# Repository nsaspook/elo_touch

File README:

Firmware to replace Implanter CRT touch monitors with LCD touch monitors. 

The ELO 19" open-frame monitor is the standard for all machines using the 19 inch rack mount as a universal adapter. Originally ELO LCD's were CarrollTouch but that was discontinued so the
emulation now is based on IntelliTouch. Now the old 1939L models are EOL so adding the 199(01)L models as the current replacement.

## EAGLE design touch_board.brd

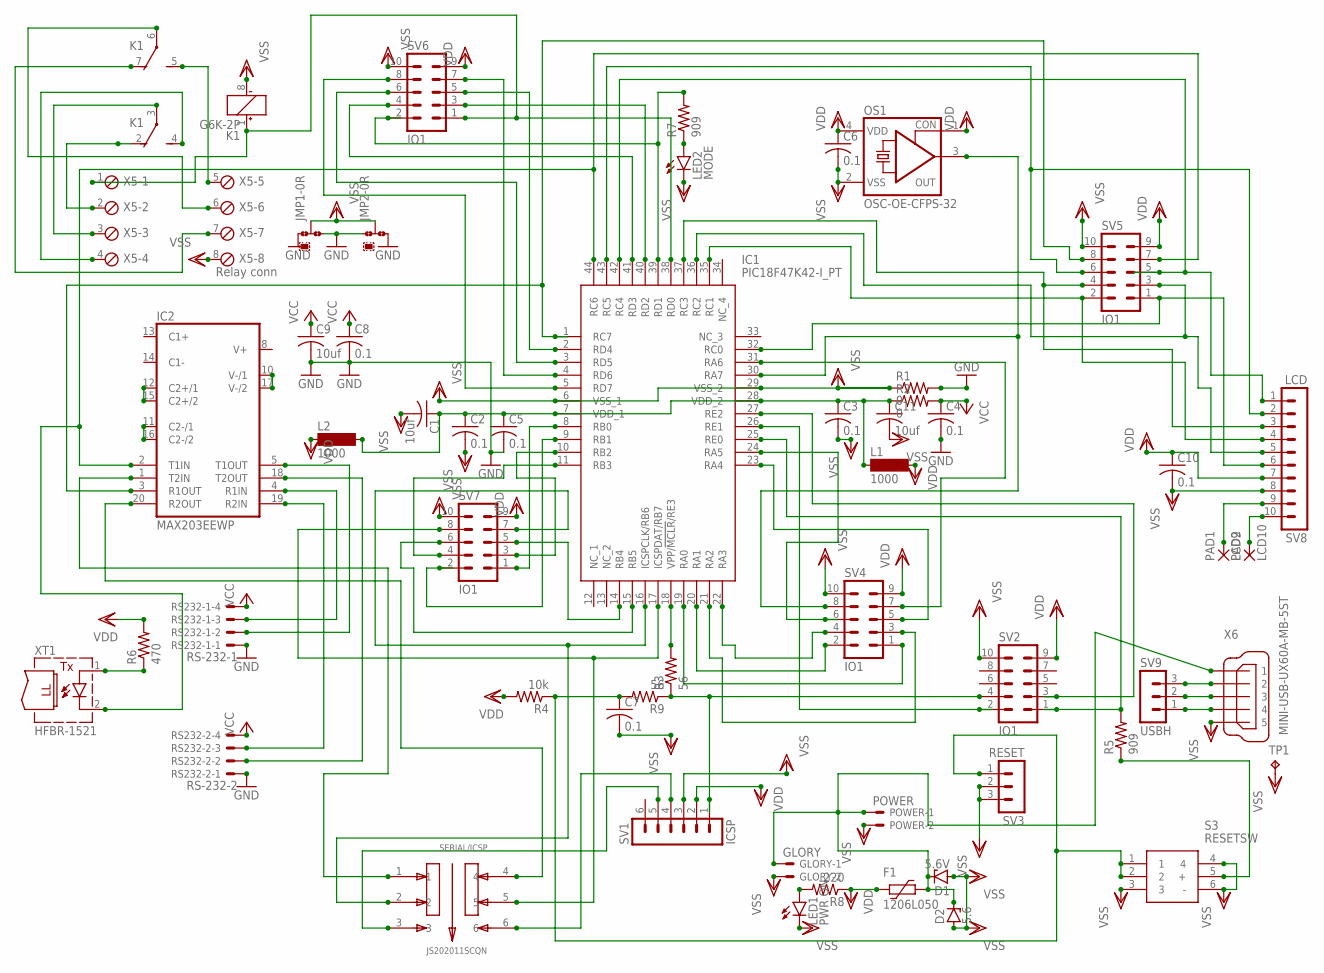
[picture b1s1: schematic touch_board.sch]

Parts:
C1, C9, C11: 10uf; C0805
C2, C3, C4, C5, C6, C7, C8, C10: 0.1; C0805
D1: 5.6V; ZDIO-7.5
D2: 5.6; SMB
F1: 1206L050; 1206L
GLORY: GLORY; 22-23-2021
IC1: PIC18F47K42-I_PT; QFP80P1200X1200X120-44N
IC2: MAX203EEWP; SO20L
JMP1, JMP2: 0R-JUMPA; A0R-JMP
K1: G6K-2P
L1, L2: 1000; SM-1206
LED1: PWR ON; CHIPLED_1206
LED2: MODE; CHIPLED_1206
OS1: OSC-OE-CFPS-32; 7.2X5.2-4-PAD
PAD1: LCD9; SMD1,27-2,54
PAD2: LCD10; SMD1,27-2,54
POWER: POWER; 22-23-2021
R1, R2: 0; R0805
R3, R9: 56; R0805
R4: 10k; R0805
R5, R7: 909; R0805
R6: 470; R0805
R8: 220; R0805
RS232-1: RS-232-1; 22-23-2041
RS232-2: RS-232-2; 22-23-2041
S3: RESETSW; B3W-9_1-LED
SERIAL/ICSP: JS202011SCQN; SW_JS202011SCQN
SV1: ICSP; MA06-1
SV2, SV4, SV5, SV6, SV7: IO1; MA05-2
SV3: RESET; MA03-1
SV8: LCD; MA10-1
SV9: USBH; MA03-1
TP1: TPB1,27; B1,27
X5: Relay conn; 8POL254
X6: MINI-USB-UX60A-MB-5ST; UX60A-MB-5ST
XT1: HFBR-1521; HFBR-15X3

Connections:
GND: C4.2, C5.2, C8.2, C9.2, IC2.6 (GND), IC2.9 (GND), JMP1.1, JMP1.3, JMP2.1, JMP2.3, R1.2, RS232-1.1, RS232-2.1
unnamed: IC1.30 (RA7), OS1.3 (OUT), SV4.8
unnamed: R3.1, R9.1, SV1.1, SV2.4
unnamed: IC1.18 (VPP/!MCLR!/RE3), R3.2
unnamed: IC1.25 (RE0), R5.2, SV2.1
unnamed: IC1.26 (RE1), SV2.2
unnamed: IC1.17 (ICSPDAT/RB7), SERIAL/ICSP.5, SV7.8
unnamed: IC1.16 (ICSPCLK/RB6), SERIAL/ICSP.2, SV7.7
unnamed: IC1.27 (RE2), SV2.3
unnamed: R5.1, S3.5 (+)
unnamed: IC1.39 (RD1), R7.2, SV6.2
unnamed: LED2.A, R7.1
unnamed: IC2.11 (C2-/1), IC2.16 (C2-/2)
unnamed: IC2.10 (V-/1), IC2.17 (V-/2)
unnamed: IC2.12 (C2+/1), IC2.15 (C2+/2)
unnamed: IC2.5 (T1OUT), RS232-1.2
unnamed: IC2.18 (T2OUT), RS232-2.2
unnamed: IC2.4 (R1IN), RS232-1.3
unnamed: IC2.19 (R2IN), RS232-2.3
unnamed: IC2.1 (T2IN), SERIAL/ICSP.1
unnamed: IC1.1 (RC7), IC2.3 (R1OUT), SV5.8
unnamed: IC2.20 (R2OUT), SERIAL/ICSP.4
unnamed: SERIAL/ICSP.6, SV1.4
unnamed: IC1.44 (RC6), IC2.2 (T1IN), SV5.7, XT1.2 (C)
unnamed: R6.1, XT1.1 (A)
unnamed: IC1.19 (RA0), SV4.1
unnamed: IC1.20 (RA1), SV4.2
unnamed: IC1.21 (RA2), SV4.3
unnamed: IC1.22 (RA3), SV4.4
unnamed: IC1.23 (RA4), SV4.5
unnamed: IC1.31 (RA6), SV4.7
unnamed: IC1.24 (RA5), SV4.6
unnamed: IC1.32 (RC0), SV5.1, SV8.6
unnamed: IC1.35 (RC1), SV5.2, SV8.4
unnamed: IC1.36 (RC2), SV5.3, SV8.5
unnamed: IC1.37 (RC3), SV5.4, SV8.3
unnamed: LED1.A, R8.2
unnamed: IC1.43 (RC5), SV5.6, SV8.2
unnamed: K1.2 (O), X5.2
unnamed: IC1.40 (RD2), SV6.3
unnamed: IC1.41 (RD3), SV6.4
unnamed: IC1.2 (RD4), SV6.5
unnamed: IC1.3 (RD5), SV6.6
unnamed: IC1.4 (RD6), SV6.7
unnamed: IC1.5 (RD7), SV6.8
unnamed: IC1.8 (RB0), SV7.1
unnamed: IC1.9 (RB1), SV7.2
unnamed: IC1.10 (RB2), SV7.3
unnamed: IC1.11 (RB3), SV7.4
unnamed: IC1.14 (RB4), SV7.5
unnamed: IC1.15 (RB5), SV7.6
unnamed: IC1.38 (RD0), K1.1 (+), SV6.1, X5.1
unnamed: K1.3, X5.3
unnamed: K1.4 (S), X5.4
unnamed: K1.5 (S), X5.5
unnamed: K1.6, X5.6
unnamed: K1.7 (O), X5.7
unnamed: C1.1, C2.1, C3.1, C5.1, C11.1, IC1.7 (VDD_1), IC1.28 (VDD_2), L1.1, L2.2, R2.1
unnamed: SV9.3, X6.2
unnamed: D1.C, D2.C, F1.1, GLORY.1, POWER.1, X6.1
unnamed: SV9.2, X6.3
unnamed: C7.1, R4.1, R9.2, S3.1, S3.2, SV3.1
unnamed: IC1.42 (RC4), SV5.5, SV8.1
unnamed: SV9.1, X6.4
unnamed: SERIAL/ICSP.3, SV1.5
unnamed: PAD1.1, SV8.9
unnamed: PAD2.1, SV8.10
VCC: C4.1, C8.1, C9.1, IC2.7 (VCC), R2.2, RS232-1.4, RS232-2.4
VDD: C6.1, C10.1, F1.2, L1.2, L2.1, OS1.1 (CON), OS1.4 (VDD), R4.2, R6.2, R8.1, SV1.2, SV2.9, SV4.9, SV5.9, SV6.9, SV7.9, SV8.7
VSS: C1.2, C2.2, C3.2, C6.2, C7.2, C10.2, C11.2, D1.A, D2.A, GLORY.2, IC1.6 (VSS_1), IC1.29 (VSS_2), JMP1.2, JMP2.2, K1.8 (-), LED1.C, LED2.C, OS1.2 (VSS), POWER.2, R1.1, S3.3, S3.4, S3.6 (-), SV1.3, SV2.10, SV3.2, SV3.3, SV4.10, SV5.10, SV6.10, SV7.10, SV8.8, TP1.TP, X5.8, X6.5

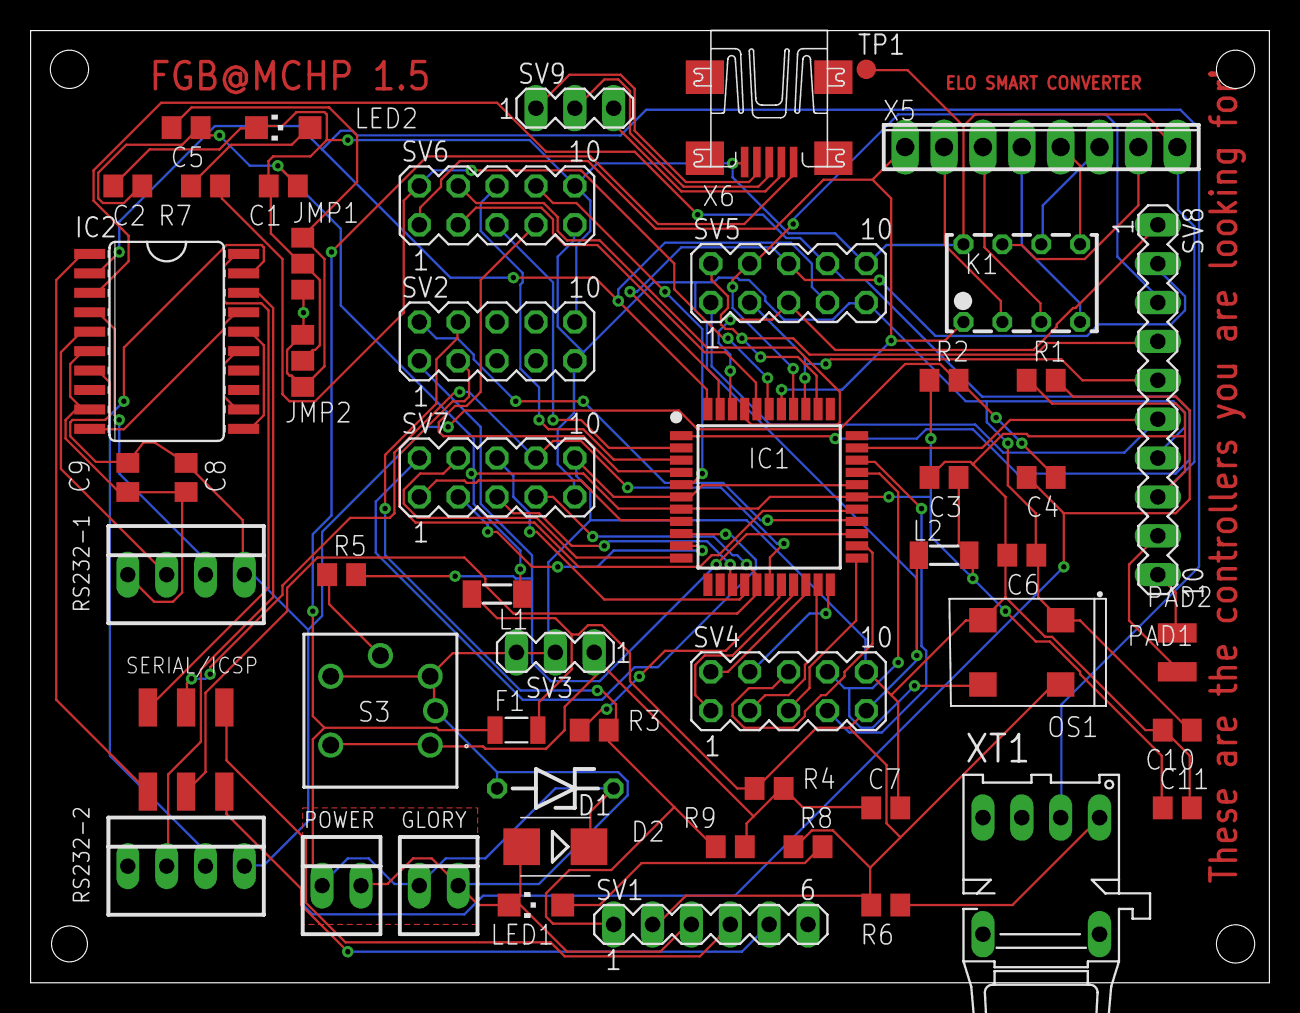
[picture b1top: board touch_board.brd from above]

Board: 2 copper layers, 81.0 x 62.2 mm, 54 parts (0 on the bottom side), 70 nets.

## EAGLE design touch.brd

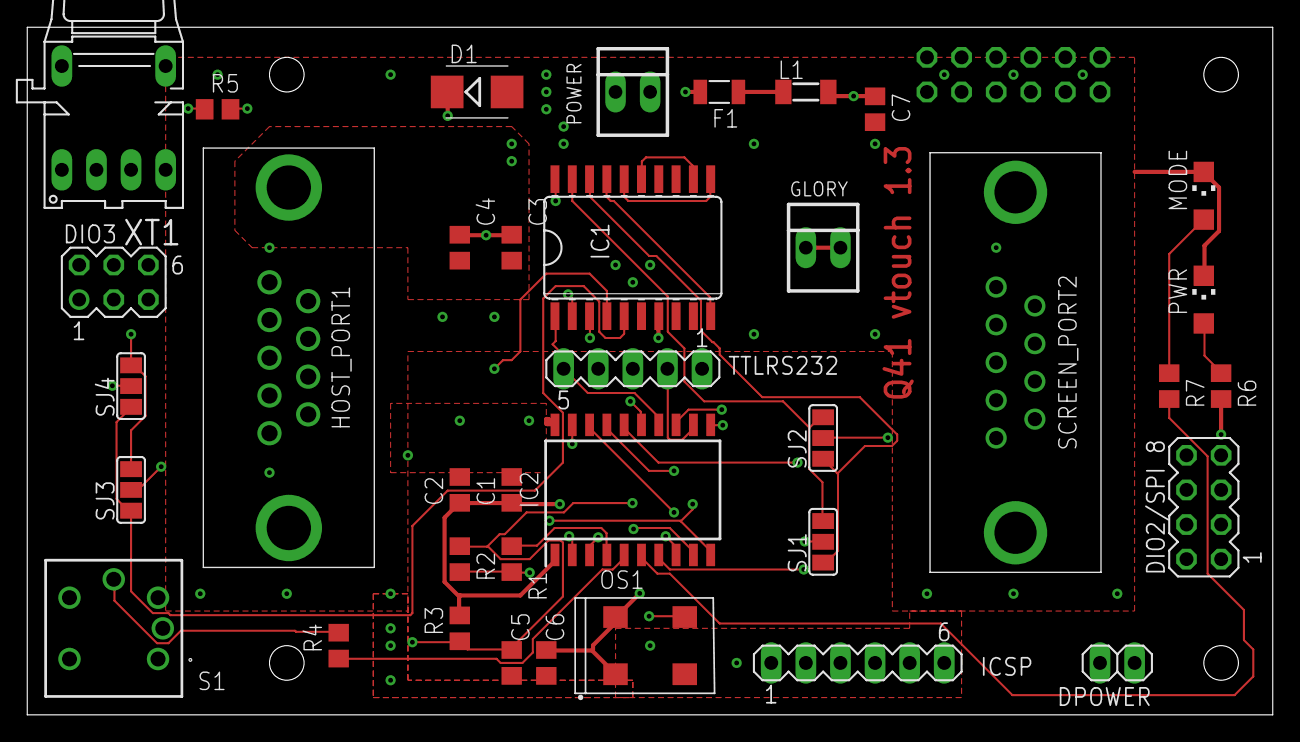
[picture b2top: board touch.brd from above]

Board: 4 copper layers, 91.4 x 50.5 mm, 38 parts (1 on the bottom side), 39 nets.

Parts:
C1: 0.1uf; C0805
C2, C4, C7: 10uf; C0805
C3, C5, C6: 0.1; C0805
D1: 5.6V; SMB
DIO2/SPI: MA04-2
DIO3: MA03-2
DPOWER: DPOWER; 1X02
F1: 0.75A; 1206L
GLORY: GLORY; 22-23-2021
HOST_PORT1: 2301838-2; 23018382
IC1: MAX203ECWP; SO20L
IC2: PIC18F14Q41-I_SO; SOIC127P1030X265-20N
ICSP: MA06-1
L1: 1000; SM-1206
MODE: Green; CHIPLED_1206
OS1: OSC-OE-CFPS-32; 7.2X5.2-4-PAD
PMOD: Pmod; MA06-2
POWER: 22-23-2021
PWR: Green; CHIPLED_1206
R1, R2: 56; R0805
R3: 10K; R0805
R4, R6, R7: 1.2k; R0805
R5: 200; R0805
S1: B3W-9000-Y1N; B3W-9_1-LED
SCREEN_PORT2: 2301826-2; 23018262
SJ1, SJ2, SJ3, SJ4: SJ_2
TTLRS232: MA05-1
XT1: HFBR-1521; HFBR-15X3

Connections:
CLKIN: DIO3.4, IC2.2, OS1.3
CS: DIO2/SPI.6, IC2.11, PMOD.1
DB0: IC2.19, ICSP.4
DB1: IC2.18, ICSP.5
GND: C1.2, C2.2, C3.2, C4.2, C5.2, C6.2, C7.2, D1.A, DIO2/SPI.2, DIO2/SPI.4, DIO3.2, DPOWER.2, HOST_PORT1.5, HOST_PORT1.MH1, HOST_PORT1.MH2, IC1.6, IC1.9, IC2.20, ICSP.3, MODE.C, OS1.2, PMOD.9, PMOD.10, POWER.2, PWR.C, S1.3, S1.4, S1.6, SCREEN_PORT2.5, SCREEN_PORT2.MH1, SCREEN_PORT2.MH2, TTLRS232.1, XT1.2
MIN0: DIO2/SPI.1, IC2.16
MIN1: DIO2/SPI.3, IC2.7
MISC: DIO3.3, IC2.10, PMOD.2
MISO: DIO2/SPI.7, IC2.13, PMOD.5
MLED: IC2.6, R7.2
MOSI: DIO2/SPI.5, IC2.17, PMOD.3
unnamed: SCREEN_PORT2.3, SJ2.2
unnamed: SCREEN_PORT2.2, SJ1.2
unnamed: HOST_PORT1.2, SJ4.2
unnamed: HOST_PORT1.3, SJ3.2
unnamed: IC1.12, IC1.15
unnamed: IC1.11, IC1.16
unnamed: IC1.10, IC1.17
unnamed: IC1.5, SJ3.1, SJ4.1
unnamed: IC1.4, SJ3.3, SJ4.3
unnamed: IC1.18, SJ1.1, SJ2.1
unnamed: IC1.19, SJ1.3, SJ2.3
unnamed: IC2.4, R1.2
unnamed: F1.2, POWER.1
unnamed: MODE.A, R7.1
unnamed: R4.2, S1.5
unnamed: R5.1, XT1.1
unnamed: F1.1, L1.1
unnamed: PWR.A, R6.1
PGM: ICSP.1, R1.1, R2.2
RELAY: DIO3.1, IC2.9, PMOD.4
RLED: IC2.5, R4.1
RX1: IC1.3, IC2.12, TTLRS232.2
RX2: IC1.20, IC2.15, TTLRS232.4
SCK: DIO2/SPI.8, IC2.3, PMOD.7
SMCLEAR: C5.1, DIO3.5, PMOD.6, R2.1, R3.1, S1.1, S1.2
TX1: IC1.2, IC2.8, PMOD.8, R5.2, TTLRS232.3
TX2: IC1.1, IC2.14, TTLRS232.5
VCC: C1.1, C2.1, C3.1, C4.1, C6.1, C7.1, D1.C, DIO3.6, DPOWER.1, GLORY.1, GLORY.2, IC1.7, IC2.1, ICSP.2, L1.2, OS1.1, OS1.4, PMOD.11, PMOD.12, R3.2, R6.2

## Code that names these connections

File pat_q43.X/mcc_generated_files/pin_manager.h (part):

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// get/set LD0 aliases
#define LD0_TRIS                 TRISAbits.TRISA0
#define LD0_LAT                  LATAbits.LATA0
#define LD0_PORT                 PORTAbits.RA0
#define LD0_WPU                  WPUAbits.WPUA0
#define LD0_OD                   ODCONAbits.ODCA0
#define LD0_ANS                  ANSELAbits.ANSELA0
#define LD0_SetHigh()            do { LATAbits.LATA0 = 1; } while(0)
#define LD0_SetLow()             do { LATAbits.LATA0 = 0; } while(0)
#define LD0_Toggle()             do { LATAbits.LATA0 = ~LATAbits.LATA0; } while(0)
#define LD0_GetValue()           PORTAbits.RA0
#define LD0_SetDigitalInput()    do { TRISAbits.TRISA0 = 1; } while(0)
#define LD0_SetDigitalOutput()   do { TRISAbits.TRISA0 = 0; } while(0)
#define LD0_SetPullup()          do { WPUAbits.WPUA0 = 1; } while(0)
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// get/set LD1 aliases
#define LD1_TRIS                 TRISAbits.TRISA1
#define LD1_LAT                  LATAbits.LATA1
#define LD1_PORT                 PORTAbits.RA1
#define LD1_WPU                  WPUAbits.WPUA1
#define LD1_OD                   ODCONAbits.ODCA1
#define LD1_ANS                  ANSELAbits.ANSELA1
#define LD1_SetHigh()            do { LATAbits.LATA1 = 1; } while(0)
#define LD1_SetLow()             do { LATAbits.LATA1 = 0; } while(0)
#define LD1_Toggle()             do { LATAbits.LATA1 = ~LATAbits.LATA1; } while(0)
#define LD1_GetValue()           PORTAbits.RA1
#define LD1_SetDigitalInput()    do { TRISAbits.TRISA1 = 1; } while(0)
#define LD1_SetDigitalOutput()   do { TRISAbits.TRISA1 = 0; } while(0)
#define LD1_SetPullup()          do { WPUAbits.WPUA1 = 1; } while(0)
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// get/set LD2 aliases
#define LD2_TRIS                 TRISAbits.TRISA2
#define LD2_LAT                  LATAbits.LATA2
#define LD2_PORT                 PORTAbits.RA2
#define LD2_WPU                  WPUAbits.WPUA2
#define LD2_OD                   ODCONAbits.ODCA2
#define LD2_ANS                  ANSELAbits.ANSELA2
#define LD2_SetHigh()            do { LATAbits.LATA2 = 1; } while(0)
#define LD2_SetLow()             do { LATAbits.LATA2 = 0; } while(0)
#define LD2_Toggle()             do { LATAbits.LATA2 = ~LATAbits.LATA2; } while(0)
#define LD2_GetValue()           PORTAbits.RA2
#define LD2_SetDigitalInput()    do { TRISAbits.TRISA2 = 1; } while(0)
#define LD2_SetDigitalOutput()   do { TRISAbits.TRISA2 = 0; } while(0)
#define LD2_SetPullup()          do { WPUAbits.WPUA2 = 1; } while(0)
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// get/set LD3 aliases
#define LD3_TRIS                 TRISAbits.TRISA3
#define LD3_LAT                  LATAbits.LATA3
#define LD3_PORT                 PORTAbits.RA3
#define LD3_WPU                  WPUAbits.WPUA3
#define LD3_OD                   ODCONAbits.ODCA3
#define LD3_ANS                  ANSELAbits.ANSELA3
#define LD3_SetHigh()            do { LATAbits.LATA3 = 1; } while(0)
#define LD3_SetLow()             do { LATAbits.LATA3 = 0; } while(0)
#define LD3_Toggle()             do { LATAbits.LATA3 = ~LATAbits.LATA3; } while(0)
#define LD3_GetValue()           PORTAbits.RA3
#define LD3_SetDigitalInput()    do { TRISAbits.TRISA3 = 1; } while(0)
#define LD3_SetDigitalOutput()   do { TRISAbits.TRISA3 = 0; } while(0)
#define LD3_SetPullup()          do { WPUAbits.WPUA3 = 1; } while(0)
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// get/set SW0 aliases
#define SW0_TRIS                 TRISBbits.TRISB0
#define SW0_LAT                  LATBbits.LATB0
#define SW0_PORT                 PORTBbits.RB0
#define SW0_WPU                  WPUBbits.WPUB0
#define SW0_OD                   ODCONBbits.ODCB0
#define SW0_ANS                  ANSELBbits.ANSELB0
#define SW0_SetHigh()            do { LATBbits.LATB0 = 1; } while(0)
#define SW0_SetLow()             do { LATBbits.LATB0 = 0; } while(0)
#define SW0_Toggle()             do { LATBbits.LATB0 = ~LATBbits.LATB0; } while(0)
#define SW0_GetValue()           PORTBbits.RB0
#define SW0_SetDigitalInput()    do { TRISBbits.TRISB0 = 1; } while(0)
#define SW0_SetDigitalOutput()   do { TRISBbits.TRISB0 = 0; } while(0)
#define SW0_SetPullup()          do { WPUBbits.WPUB0 = 1; } while(0)
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// get/set SW1 aliases
#define SW1_TRIS                 TRISBbits.TRISB1
#define SW1_LAT                  LATBbits.LATB1
#define SW1_PORT                 PORTBbits.RB1
#define SW1_WPU                  WPUBbits.WPUB1
#define SW1_OD                   ODCONBbits.ODCB1
#define SW1_ANS                  ANSELBbits.ANSELB1
#define SW1_SetHigh()            do { LATBbits.LATB1 = 1; } while(0)
#define SW1_SetLow()             do { LATBbits.LATB1 = 0; } while(0)
#define SW1_Toggle()             do { LATBbits.LATB1 = ~LATBbits.LATB1; } while(0)
#define SW1_GetValue()           PORTBbits.RB1
#define SW1_SetDigitalInput()    do { TRISBbits.TRISB1 = 1; } while(0)
#define SW1_SetDigitalOutput()   do { TRISBbits.TRISB1 = 0; } while(0)
#define SW1_SetPullup()          do { WPUBbits.WPUB1 = 1; } while(0)
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// get/set SW2 aliases
#define SW2_TRIS                 TRISBbits.TRISB2
#define SW2_LAT                  LATBbits.LATB2
#define SW2_PORT                 PORTBbits.RB2
#define SW2_WPU                  WPUBbits.WPUB2
#define SW2_OD                   ODCONBbits.ODCB2
#define SW2_ANS                  ANSELBbits.ANSELB2
#define SW2_SetHigh()            do { LATBbits.LATB2 = 1; } while(0)
#define SW2_SetLow()             do { LATBbits.LATB2 = 0; } while(0)
#define SW2_Toggle()             do { LATBbits.LATB2 = ~LATBbits.LATB2; } while(0)
#define SW2_GetValue()           PORTBbits.RB2
#define SW2_SetDigitalInput()    do { TRISBbits.TRISB2 = 1; } while(0)
#define SW2_SetDigitalOutput()   do { TRISBbits.TRISB2 = 0; } while(0)
#define SW2_SetPullup()          do { WPUBbits.WPUB2 = 1; } while(0)
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// get/set SW3 aliases
#define SW3_TRIS                 TRISBbits.TRISB3
#define SW3_LAT                  LATBbits.LATB3
#define SW3_PORT                 PORTBbits.RB3
#define SW3_WPU                  WPUBbits.WPUB3
#define SW3_OD                   ODCONBbits.ODCB3
#define SW3_ANS                  ANSELBbits.ANSELB3
#define SW3_SetHigh()            do { LATBbits.LATB3 = 1; } while(0)
#define SW3_SetLow()             do { LATBbits.LATB3 = 0; } while(0)
#define SW3_Toggle()             do { LATBbits.LATB3 = ~LATBbits.LATB3; } while(0)
#define SW3_GetValue()           PORTBbits.RB3
#define SW3_SetDigitalInput()    do { TRISBbits.TRISB3 = 1; } while(0)
#define SW3_SetDigitalOutput()   do { TRISBbits.TRISB3 = 0; } while(0)
#define SW3_SetPullup()          do { WPUBbits.WPUB3 = 1; } while(0)
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// get/set ID0 aliases
#define ID0_TRIS                 TRISBbits.TRISB4
#define ID0_LAT                  LATBbits.LATB4
#define ID0_PORT                 PORTBbits.RB4
#define ID0_WPU                  WPUBbits.WPUB4
#define ID0_OD                   ODCONBbits.ODCB4
#define ID0_ANS                  ANSELBbits.ANSELB4
#define ID0_SetHigh()            do { LATBbits.LATB4 = 1; } while(0)
#define ID0_SetLow()             do { LATBbits.LATB4 = 0; } while(0)
#define ID0_Toggle()             do { LATBbits.LATB4 = ~LATBbits.LATB4; } while(0)
#define ID0_GetValue()           PORTBbits.RB4
#define ID0_SetDigitalInput()    do { TRISBbits.TRISB4 = 1; } while(0)
#define ID0_SetDigitalOutput()   do { TRISBbits.TRISB4 = 0; } while(0)
#define ID0_SetPullup()          do { WPUBbits.WPUB4 = 1; } while(0)
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// get/set ID1 aliases
#define ID1_TRIS                 TRISBbits.TRISB5
#define ID1_LAT                  LATBbits.LATB5
#define ID1_PORT                 PORTBbits.RB5
#define ID1_WPU                  WPUBbits.WPUB5
#define ID1_OD                   ODCONBbits.ODCB5
#define ID1_ANS                  ANSELBbits.ANSELB5
#define ID1_SetHigh()            do { LATBbits.LATB5 = 1; } while(0)
#define ID1_SetLow()             do { LATBbits.LATB5 = 0; } while(0)
#define ID1_Toggle()             do { LATBbits.LATB5 = ~LATBbits.LATB5; } while(0)
#define ID1_GetValue()           PORTBbits.RB5
#define ID1_SetDigitalInput()    do { TRISBbits.TRISB5 = 1; } while(0)
#define ID1_SetDigitalOutput()   do { TRISBbits.TRISB5 = 0; } while(0)
#define ID1_SetPullup()          do { WPUBbits.WPUB5 = 1; } while(0)
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// get/set ID2 aliases
#define ID2_TRIS                 TRISBbits.TRISB6
#define ID2_LAT                  LATBbits.LATB6
#define ID2_PORT                 PORTBbits.RB6
#define ID2_WPU                  WPUBbits.WPUB6
#define ID2_OD                   ODCONBbits.ODCB6
#define ID2_ANS                  ANSELBbits.ANSELB6
#define ID2_SetHigh()            do { LATBbits.LATB6 = 1; } while(0)
#define ID2_SetLow()             do { LATBbits.LATB6 = 0; } while(0)
#define ID2_Toggle()             do { LATBbits.LATB6 = ~LATBbits.LATB6; } while(0)
#define ID2_GetValue()           PORTBbits.RB6
#define ID2_SetDigitalInput()    do { TRISBbits.TRISB6 = 1; } while(0)
#define ID2_SetDigitalOutput()   do { TRISBbits.TRISB6 = 0; } while(0)
#define ID2_SetPullup()          do { WPUBbits.WPUB6 = 1; } while(0)
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// get/set ID3 aliases
#define ID3_TRIS                 TRISBbits.TRISB7
#define ID3_LAT                  LATBbits.LATB7
#define ID3_PORT                 PORTBbits.RB7
#define ID3_WPU                  WPUBbits.WPUB7
#define ID3_OD                   ODCONBbits.ODCB7
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
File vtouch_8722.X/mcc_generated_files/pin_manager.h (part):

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// get/set JMP1 aliases
#define JMP1_TRIS                 TRISAbits.TRISA0
#define JMP1_LAT                  LATAbits.LATA0
#define JMP1_PORT                 PORTAbits.RA0
#define JMP1_WPU                  WPUAbits.WPUA0
#define JMP1_OD                   ODCONAbits.ODCA0
#define JMP1_ANS                  ANSELAbits.ANSELA0
#define JMP1_SetHigh()            do { LATAbits.LATA0 = 1; } while(0)
#define JMP1_SetLow()             do { LATAbits.LATA0 = 0; } while(0)
#define JMP1_Toggle()             do { LATAbits.LATA0 = ~LATAbits.LATA0; } while(0)
#define JMP1_GetValue()           PORTAbits.RA0
#define JMP1_SetDigitalInput()    do { TRISAbits.TRISA0 = 1; } while(0)
#define JMP1_SetDigitalOutput()   do { TRISAbits.TRISA0 = 0; } while(0)
#define JMP1_SetPullup()          do { WPUAbits.WPUA0 = 1; } while(0)
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// get/set JMP1SET aliases
#define JMP1SET_TRIS                 TRISAbits.TRISA1
#define JMP1SET_LAT                  LATAbits.LATA1
#define JMP1SET_PORT                 PORTAbits.RA1
#define JMP1SET_WPU                  WPUAbits.WPUA1
#define JMP1SET_OD                   ODCONAbits.ODCA1
#define JMP1SET_ANS                  ANSELAbits.ANSELA1
#define JMP1SET_SetHigh()            do { LATAbits.LATA1 = 1; } while(0)
#define JMP1SET_SetLow()             do { LATAbits.LATA1 = 0; } while(0)
#define JMP1SET_Toggle()             do { LATAbits.LATA1 = ~LATAbits.LATA1; } while(0)
#define JMP1SET_GetValue()           PORTAbits.RA1
#define JMP1SET_SetDigitalInput()    do { TRISAbits.TRISA1 = 1; } while(0)
#define JMP1SET_SetDigitalOutput()   do { TRISAbits.TRISA1 = 0; } while(0)
#define JMP1SET_SetPullup()          do { WPUAbits.WPUA1 = 1; } while(0)
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// get/set JMP2 aliases
#define JMP2_TRIS                 TRISAbits.TRISA2
#define JMP2_LAT                  LATAbits.LATA2
#define JMP2_PORT                 PORTAbits.RA2
#define JMP2_WPU                  WPUAbits.WPUA2
#define JMP2_OD                   ODCONAbits.ODCA2
#define JMP2_ANS                  ANSELAbits.ANSELA2
#define JMP2_SetHigh()            do { LATAbits.LATA2 = 1; } while(0)
#define JMP2_SetLow()             do { LATAbits.LATA2 = 0; } while(0)
#define JMP2_Toggle()             do { LATAbits.LATA2 = ~LATAbits.LATA2; } while(0)
#define JMP2_GetValue()           PORTAbits.RA2
#define JMP2_SetDigitalInput()    do { TRISAbits.TRISA2 = 1; } while(0)
#define JMP2_SetDigitalOutput()   do { TRISAbits.TRISA2 = 0; } while(0)
#define JMP2_SetPullup()          do { WPUAbits.WPUA2 = 1; } while(0)
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// get/set JMP2SET aliases
#define JMP2SET_TRIS                 TRISAbits.TRISA3
#define JMP2SET_LAT                  LATAbits.LATA3
#define JMP2SET_PORT                 PORTAbits.RA3
#define JMP2SET_WPU                  WPUAbits.WPUA3
#define JMP2SET_OD                   ODCONAbits.ODCA3
#define JMP2SET_ANS                  ANSELAbits.ANSELA3
#define JMP2SET_SetHigh()            do { LATAbits.LATA3 = 1; } while(0)
#define JMP2SET_SetLow()             do { LATAbits.LATA3 = 0; } while(0)
#define JMP2SET_Toggle()             do { LATAbits.LATA3 = ~LATAbits.LATA3; } while(0)
#define JMP2SET_GetValue()           PORTAbits.RA3
#define JMP2SET_SetDigitalInput()    do { TRISAbits.TRISA3 = 1; } while(0)
#define JMP2SET_SetDigitalOutput()   do { TRISAbits.TRISA3 = 0; } while(0)
#define JMP2SET_SetPullup()          do { WPUAbits.WPUA3 = 1; } while(0)
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// get/set CAM_R aliases
#define CAM_R_TRIS                 TRISBbits.TRISB0
#define CAM_R_LAT                  LATBbits.LATB0
#define CAM_R_PORT                 PORTBbits.RB0
#define CAM_R_WPU                  WPUBbits.WPUB0
#define CAM_R_OD                   ODCONBbits.ODCB0
#define CAM_R_ANS                  ANSELBbits.ANSELB0
#define CAM_R_SetHigh()            do { LATBbits.LATB0 = 1; } while(0)
#define CAM_R_SetLow()             do { LATBbits.LATB0 = 0; } while(0)
#define CAM_R_Toggle()             do { LATBbits.LATB0 = ~LATBbits.LATB0; } while(0)
#define CAM_R_GetValue()           PORTBbits.RB0
#define CAM_R_SetDigitalInput()    do { TRISBbits.TRISB0 = 1; } while(0)
#define CAM_R_SetDigitalOutput()   do { TRISBbits.TRISB0 = 0; } while(0)
#define CAM_R_SetPullup()          do { WPUBbits.WPUB0 = 1; } while(0)
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// get/set CAM_R1 aliases
#define CAM_R1_TRIS                 TRISBbits.TRISB1
#define CAM_R1_LAT                  LATBbits.LATB1
#define CAM_R1_PORT                 PORTBbits.RB1
#define CAM_R1_WPU                  WPUBbits.WPUB1
#define CAM_R1_OD                   ODCONBbits.ODCB1
#define CAM_R1_ANS                  ANSELBbits.ANSELB1
#define CAM_R1_SetHigh()            do { LATBbits.LATB1 = 1; } while(0)
#define CAM_R1_SetLow()             do { LATBbits.LATB1 = 0; } while(0)
#define CAM_R1_Toggle()             do { LATBbits.LATB1 = ~LATBbits.LATB1; } while(0)
#define CAM_R1_GetValue()           PORTBbits.RB1
#define CAM_R1_SetDigitalInput()    do { TRISBbits.TRISB1 = 1; } while(0)
#define CAM_R1_SetDigitalOutput()   do { TRISBbits.TRISB1 = 0; } while(0)
#define CAM_R1_SetPullup()          do { WPUBbits.WPUB1 = 1; } while(0)
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#define RB6_SetHigh()            do { LATBbits.LATB6 = 1; } while(0)
#define RB6_SetLow()             do { LATBbits.LATB6 = 0; } while(0)
#define RB6_Toggle()             do { LATBbits.LATB6 = ~LATBbits.LATB6; } while(0)
#define RB6_GetValue()              PORTBbits.RB6
#define RB6_SetDigitalInput()    do { TRISBbits.TRISB6 = 1; } while(0)
#define RB6_SetDigitalOutput()   do { TRISBbits.TRISB6 = 0; } while(0)
#define RB6_SetPullup()             do { WPUBbits.WPUB6 = 1; } while(0)
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#define RB7_SetHigh()            do { LATBbits.LATB7 = 1; } while(0)
#define RB7_SetLow()             do { LATBbits.LATB7 = 0; } while(0)
#define RB7_Toggle()             do { LATBbits.LATB7 = ~LATBbits.LATB7; } while(0)
#define RB7_GetValue()              PORTBbits.RB7
#define RB7_SetDigitalInput()    do { TRISBbits.TRISB7 = 1; } while(0)
#define RB7_SetDigitalOutput()   do { TRISBbits.TRISB7 = 0; } while(0)
#define RB7_SetPullup()             do { WPUBbits.WPUB7 = 1; } while(0)
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// get/set RS aliases
#define RS_TRIS                 TRISCbits.TRISC1
#define RS_LAT                  LATCbits.LATC1
#define RS_PORT                 PORTCbits.RC1
#define RS_WPU                  WPUCbits.WPUC1
#define RS_OD                   ODCONCbits.ODCC1
#define RS_ANS                  ANSELCbits.ANSELC1
#define RS_SetHigh()            do { LATCbits.LATC1 = 1; } while(0)
#define RS_SetLow()             do { LATCbits.LATC1 = 0; } while(0)
#define RS_Toggle()             do { LATCbits.LATC1 = ~LATCbits.LATC1; } while(0)
#define RS_GetValue()           PORTCbits.RC1
#define RS_SetDigitalInput()    do { TRISCbits.TRISC1 = 1; } while(0)
#define RS_SetDigitalOutput()   do { TRISCbits.TRISC1 = 0; } while(0)
#define RS_SetPullup()          do { WPUCbits.WPUC1 = 1; } while(0)
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// get/set CSB aliases
#define CSB_TRIS                 TRISCbits.TRISC2
#define CSB_LAT                  LATCbits.LATC2
#define CSB_PORT                 PORTCbits.RC2
#define CSB_WPU                  WPUCbits.WPUC2
#define CSB_OD                   ODCONCbits.ODCC2
#define CSB_ANS                  ANSELCbits.ANSELC2
#define CSB_SetHigh()            do { LATCbits.LATC2 = 1; } while(0)
#define CSB_SetLow()             do { LATCbits.LATC2 = 0; } while(0)
#define CSB_Toggle()             do { LATCbits.LATC2 = ~LATCbits.LATC2; } while(0)
#define CSB_GetValue()           PORTCbits.RC2
#define CSB_SetDigitalInput()    do { TRISCbits.TRISC2 = 1; } while(0)
#define CSB_SetDigitalOutput()   do { TRISCbits.TRISC2 = 0; } while(0)
#define CSB_SetPullup()          do { WPUCbits.WPUC2 = 1; } while(0)
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#define RC3_SetHigh()            do { LATCbits.LATC3 = 1; } while(0)
#define RC3_SetLow()             do { LATCbits.LATC3 = 0; } while(0)
#define RC3_Toggle()             do { LATCbits.LATC3 = ~LATCbits.LATC3; } while(0)
#define RC3_GetValue()              PORTCbits.RC3
#define RC3_SetDigitalInput()    do { TRISCbits.TRISC3 = 1; } while(0)
#define RC3_SetDigitalOutput()   do { TRISCbits.TRISC3 = 0; } while(0)
#define RC3_SetPullup()             do { WPUCbits.WPUC3 = 1; } while(0)
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#define RC4_SetHigh()            do { LATCbits.LATC4 = 1; } while(0)
#define RC4_SetLow()             do { LATCbits.LATC4 = 0; } while(0)
#define RC4_Toggle()             do { LATCbits.LATC4 = ~LATCbits.LATC4; } while(0)
#define RC4_GetValue()              PORTCbits.RC4
#define RC4_SetDigitalInput()    do { TRISCbits.TRISC4 = 1; } while(0)
#define RC4_SetDigitalOutput()   do { TRISCbits.TRISC4 = 0; } while(0)
#define RC4_SetPullup()             do { WPUCbits.WPUC4 = 1; } while(0)
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#define RC5_SetHigh()            do { LATCbits.LATC5 = 1; } while(0)
#define RC5_SetLow()             do { LATCbits.LATC5 = 0; } while(0)
#define RC5_Toggle()             do { LATCbits.LATC5 = ~LATCbits.LATC5; } while(0)
#define RC5_GetValue()              PORTCbits.RC5
#define RC5_SetDigitalInput()    do { TRISCbits.TRISC5 = 1; } while(0)
#define RC5_SetDigitalOutput()   do { TRISCbits.TRISC5 = 0; } while(0)
#define RC5_SetPullup()             do { WPUCbits.WPUC5 = 1; } while(0)
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#define RC6_SetHigh()            do { LATCbits.LATC6 = 1; } while(0)
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
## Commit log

2018-06-17 3.35 update
2024-12-09 rename to vtouch_Q41

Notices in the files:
pat_q43.X/mcc_generated_files/pin_manager.h:
(c) 2018 Microchip Technology Inc. and its subsidiaries.
